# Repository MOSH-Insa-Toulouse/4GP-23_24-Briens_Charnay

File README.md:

# 4GP-23_24-Briens_Charnay

Projet réalisé sur l'année universitaire 2023/2024 de la formation 4GP, dans le cadre de l'Unité de Formation (UF) "du capteur au banc de test".
Le ci-présent fichier README donne tous les éléments de compréhension du projet global, ainsi que de toutes ses composantes. Cela est réalisé de sorte à permettre à l'utilisateur de reprendre tous les fichiers du présent dépôt GitHub, et de s'en servir.

## Sommaire

 - [Introduction](#introduction)
 - [Capteur à base de crayon graphite](#capteur-graphite)
 - [Circuit Electronique Analogique](#circuit-electronique-analogique)
 - [Kicad : réalisation du shield électronique PCB](#kicad)
 - [Banc de test](#banc-de-test)
 - [Interface Homme-Machine](#ihm)
 - [Programmation](#programmation)
 - [Datasheet](#datasheet)
***
## Introduction
### Contexte du projet

Nos travaux se sont basés sur les résultats d'une publication scientifique \[Cheng-Wei Lin et al., 2014]. Celle-ci étudiait l'utilisation de pistes de graphites sur des feuilles de papier comme capteurs de déformation, et donc de contrainte. Une telle technologie aurait de nombreux avantages :
 - Elle est sobre ;
 - Elle consomme peu d'énergie ;
 - Elle est simple d'utilisation ;
 - Elle est facilement réparable et remplaçable avec peu de ressources ;
 - Les ressources nécessaires sont disponibles au grand public pour un prix très réduit.

Du point de vue physique, la technologie se base sur les effets granulaires des couches de graphite déposées sur le papier : qui agissent comme des îlots conducteurs, séparés par une absence de graphite - non conductrice. Cela induit d'infimes capacités en très grand nombre. Lorsque le papier est déformé, la distance entre ces îlots varie, les capacités également. Cela se mesure sur la résistance du dispositif : dont l'évolution angulaire absolue varie linéairement.

### Contenu du projet

Comme annoncé par le nom de l'UF, notre projet a inclut toutes les étapes allant du capteur au bac de test, le tout en open source hardware. Les différentes phases clés du projet ont donc été, telles qu'annoncées en sommaire :
- le développement du capteur à jauge de contrainte à base de crayon graphite ;
- la conception d'un circuit analogique pour interfacer le capteur à jauge de contrainte;
- la programmation arduino de microcontrôleurs ;
- la réalisation d'une application android ;
- la réalisation d'un shield électronique PCB dédié à l'interface du capteur de contrainte ;
- la réalisation d'un banc de test.

Ces différentes étapes ne seront pas présentées dans un ordre temporel mais logique : de sorte à permettre pour chacune de comprendre l'intégralité des éléments.
***
## Capteur graphite
Le capteur graphite développé se présente sous la forme suivante, toutes les grandeurs sont données en mm :

On note le signal prévu pour chacun des pins :
- pin 1 : +5V
- pin 2 : sortie analogique
Les deux pins sont inversibles.

Les zones pointillées doivent être recouverte d'une épaisse couche de graphite, déposée par crayon.
Les pins utilisés sont supposés classiques, comme par exemple des pinces métalliques.
***
## Circuit Electronique Analogique

L'impédance de notre capteur graphite est de l'ordre du gigaOhm, les courants et les variations de courant à mesurer seront donc très faible. Afin que l'entrée convertisseur analogique numérique de l'arduino puisse détecter ces variations de tension, nous avons dû réaliser un circuit d'amplification. Nous avons choisi un montage transimpédance à deux étages en utilisant l'amplificateur opérationnel LTC 1050. Ce montage permet de convertir le courant en tension ainsi que de réaliser un gain conséquent. Le montage final, présenté ci-dessous, inclut aussi plusieurs filtres :

- R5 en entrée protège l'ampli opérationnel contre les décharges électrostatiques, en
forme avec C1 un filtre pour les bruits en tension
- C1 avec R1 forme un filtre pour le bruit en courant
- R2 sera interchangeable, pour permettre une adaptation du calibre
- C4 avec R3 forme un filtre actif
- C2 avec R6 forme le filtre de sortie
- C3 filtre le bruit d'alimentation

*Fichier associé* : Circuit_capteur_final.asc

***
## Kicad
La réalisation du shield électronique PCB nous avons utilisé le logiciel Kicad 8.0.

### Schematic

La première étape a été de réaliser le schematic du circuit electronique analogique en implantant les différents composants que nous avons vu dans la partie cirtuit electronique analogique. Nous avons uniquement remplacé le résistance R2 par le potentiomètre digital MCP-41050. Cela nous permet de faire varier la résistance R2 et donc d'avoir la possibilité de jouer sur le gain de l'amplificateur.

Nous avons ajouté plusieurs composants :

- Le capteur graphite
- Un capteur flex dans le but de le comparer avec notre solution lowtech
- Un écran OLED afin d'afficher les valeurs mesurées ainsi que la valeur de résistance du potentiomètre digital.
- Un module bluetooth HC-6 pour pouvoir communiquer avec une application Android
- Des boutons qui permettrons de se déplacer dans le menu et de selectionner un champ
- Le shield pour connecter l'arduino
- Un filtre passif pour les bruits venant de l'alimentation

*Fichier associé* : Shield_capteur.kicad_sch

***
### PCB

Nous avons ensuite pu implanter les différents composants sur le PCB comme présenté ci-dessous.

Les dimensionnements sont les suivants :
- La largeur des pistes est de 0,8mm
- Les pads circulaires pour les composants ont un diamètre de 2,54mm avec un trou circulaire de 0,8mm
- Les pads ovoïde pour les raccordements par pins ont une largeur de 2mm et une longueur de 2,54mm. Les pins de raccordements pour l'arduino nécessite un trou de 1mm de diamètre. Les pads pour les supports de plaques ont quand à eux un trou de 0,8mm

  Le plan de masse a été généré automatiquement par Kicad. En effectuant le test de vérification des règles de dessin, nous avons pu corriger des erreurs de placement ou de superposition des composants.
L'organisation de notre PCB nous a permis de ne pas avoir besoin de créer des VIAs. Nous avons ensuite pu imprimer le masque de notre circuit afin de réaliser le shield par voie chimique.

*Fichier associé* : Shield_capteur.kicad_pcb

***
## Banc de test

Afin de réaliser des mesures précises et reproductibles, nous avons réalisé un banc de test complet. Celui-ci est composé de différents composants présentés ci-dessous :

Comme présenté sur la photo détaillée, nous avons utilisé un second arduino pour réaliser notre banc de test. Ce dernier contrôle le servomoteur qui permet l'enroulement d'un cable autour d'une poulie. Cela permet de plier d'un pas choisi, de manière très contrôlé et reproductible le capteur graphite. Ce second arduino est branché sur les pins l'arduino principal afin qu'une synchronisation entre les changements de degrés et la mesure puisse s'effectuer. Vous trouverez plus de détails sur la communication entre les deux arduino dans la partie programmation. 

***
## IHM
L'Interface Homme-Machine (ou IHM) correspond à tous les éléments permettant la communication entre l'utilisateur et les composants software.
### Boutons et écran OLED
Trois boutons ainsi qu'un écran OLED sont directement présents sur le shield :

Du haut vers le bas, les trois boutons correspondent aux actions :
- select ;
- up ;
- down.

L'écran OLED affiche un total de 4 champs. Les deux premiers sont modifiables, les deux derniers correspondent à des mesures réalisées.
- la valeur du potentiomètre digital ;
- l'unité de mesure ;
- la valeur mesurée dans cette unité par le capteur graphite ;
- la valeur mesurée dans cette unité par le Flex Sensor, capteur commercial.

L'utilisateur contrôle un curseur, celui-ci a deux états disponibles : "- xyz -" et "< xyz >". Le premier correspond au choix du champ à modifier : il permet à l'utilisateur de choisir s'il souhait modifier la valeur du potentiomètre ou l'unité de mesure. Le deuxième correspond à la modification du champ actuel : les boutons up et down permettent alors de se déplacer parmis les différentes options proposées pour le champ actuel. La pression du bouton select permet de passer d'un état à l'autre.
### Application Android
Il est également possible de communiquer avec l'arduino via une application android connectée en bluetooth. Celle-ci se présente ainsi :

Chaque ligne possède un rôle :
- la première, "Bluetooth et fichier" : permet de se connecter à l'arduino en bluetooth, de s'en déconnecter, et d'exporter les données du graphe. L'export se fait dans un fichier texte généré dans le téléphone ;
- la deuxième, "Contrôle d'acquisition" : permet de lancer l'acquisition de données, de la stopper, ou de lancer un test automatisé de la jauge (voir banc de test) ;
- la troisième est le graphe sur lequel apparaissent les données récoltées ;
- la quatrième, "Contrôle graphique" : permet de remettre le graphique à zéro, et de changer l'unité de mesure en volts, en ohms, ou en degrés ;
- la cinquième, "Nombre de points" : permet de choisir le nombre de point maximum à enregistrer et afficher sur le graphique.

*Fichiers associés* :
- application android/AppMOSH1.apk
- application android/CodeAppAndroid.aia
***
## Programmation
### Protocoles de communication
Au sein de notre projet, nous avons mis en place deux protocoles de communication : entre le téléphone et l'arduino du capteur graphite (bluetooth), ainsi qu'entre cette dernière et l'arduino du banc de test (électronique directe).
#### Communication Bluetooth
Dans le cadre de la communication bluetooth entre le téléphone et l'arduino du capteur graphite, les données sont transmises sous format ASCII, par des messages de 16 caractères, sous le format suivent :

Le téléphone est maître de la communication, l'arduino joue le rôle d'esclave. Le caractère "commande" permet de transmettre une information ou ordre spécifique, nous notons les différentes possibilités :

Du téléphone vers l'arduino :
- d : demander l'envoie d'un message ;
- V : choix d'une mesure en volts ;
- O : choix d'une mesure en ohms ;
- D : choix d'une mesure en degrés ;
- t : lancement d'un test automatisé.

De l'arduino vers le téléphone :
- V : message contenant une donnée en volts ;
- O : message contenant une donnée en ohms ;
- D : message contenant une donnée en degrés ;
- c : information du lancement d'un test automatisé ;
- f : information de la fin d'un test automatisé.
#### Communication électronique directe
Dans le cadre de la communication électronique directe entre les arduinos du capteur graphite et du banc de test, deux lignes de communication sont utilisées : chacune contrôlée par une carte arduino. Ce protocole de communication permet de synchroniser le lancement des tests automatisés entre le banc de test, et l'enregistrement des mesures sur le téléphone. Le chronogramme se présente ainsi :

Nous détaillons chaque évolution :
- état initial : les deux lignes sont à l'état down ;
- l'arduino du capteur reçoit l'ordre de l'application de lancer le test automatisé, sa ligne passe à up ;
- l'arduino du banc de test lit l'information, lance le test, et passe sa ligne à up ;
- l'arduino du capteur lit que le test a bien été lancé, passe sa ligne à down, et envoie l'information à l'application ;
- une fois le test terminé, l'arduino du banc de test passe sa ligne à down ;
- l'arduino du capteur lit que le test est terminé, et envoie l'information à l'application.
### Programme Arduino
Deux programmes arduinos ont été créés, pour les deux cartes utilisées dans ce projet : celle du shield PCB (connectée au capteur graphite), et celle du banc de test. Nous détaillons leur fonctionnement.
#### Arduino du capteur graphite
Le fonctionnement général de l'arduino du capteur graphite suit la logique présentée dans le schéma suivant :

Le choix a été fait de réaliser un debouncing des boutons entièrement software.

*Fichier associé* : programme_complet/programme_complet.ino
#### Arduino du banc de test
L'arduino du banc de test possède un programme bien plus simple et direct. Celui-ci suit la structure suivante :
- ajuster la position du Servomoteur : à 0 si aucun test n'est en cours, sinon une autre valeur variable ;
- lire et écrire sur les lignes de communication avec l'arduino du capteur graphite.

*Fichier associé* : programme_second_arduino/prog_second_arduino/prog_second_arduino.ino
***
## Datasheet
Finalement, la combinaison de tous ces éléments a permis la récolte de données, et la rédaction d'une datasheet complète du capteur graphite. Celle-ci est divisée en plusieurs catégories :
- Caractéristiques générales : points clés à l'avantage du capteur ;
- Description : description de la physique du fonctionnement du capteur, développement de ses avantages clés, objectif du développement du capteur ;
- Description des pins : description des pins et signaux du capteur, permettant son implémentation électronique ;
- Dimensions : description matérielle du capteur ;
- Spécifications : description technique concise du capteur ;
- Conditions d'utilisation standard : conditions environnementales classiques, pour lesquelles le capteur a été développé ;
- Caractéristiques électriques : pour les différentes variantes du capteur (en fonction du crayon utilisé), évolution de la résistance absolue et relative en fonction de l'angle ;
- Utilisation typique : exemple d'un circuit électronique typique dans lequel implémenter le capteur pour en tirer des données.
Ce circuit électronique typique correspond à celui que nous avons réalisé sur l'arduino du capteur, et présenté précédemment.

Cette datasheet permet à tout nouvel arrivant de produire et d'utiliser notre capteur graphite : dans un esprit Low-Tech et Open Source.

*Fichier associé* : Datasheet_strain_gauge-MCharnay-ABriens.pdf

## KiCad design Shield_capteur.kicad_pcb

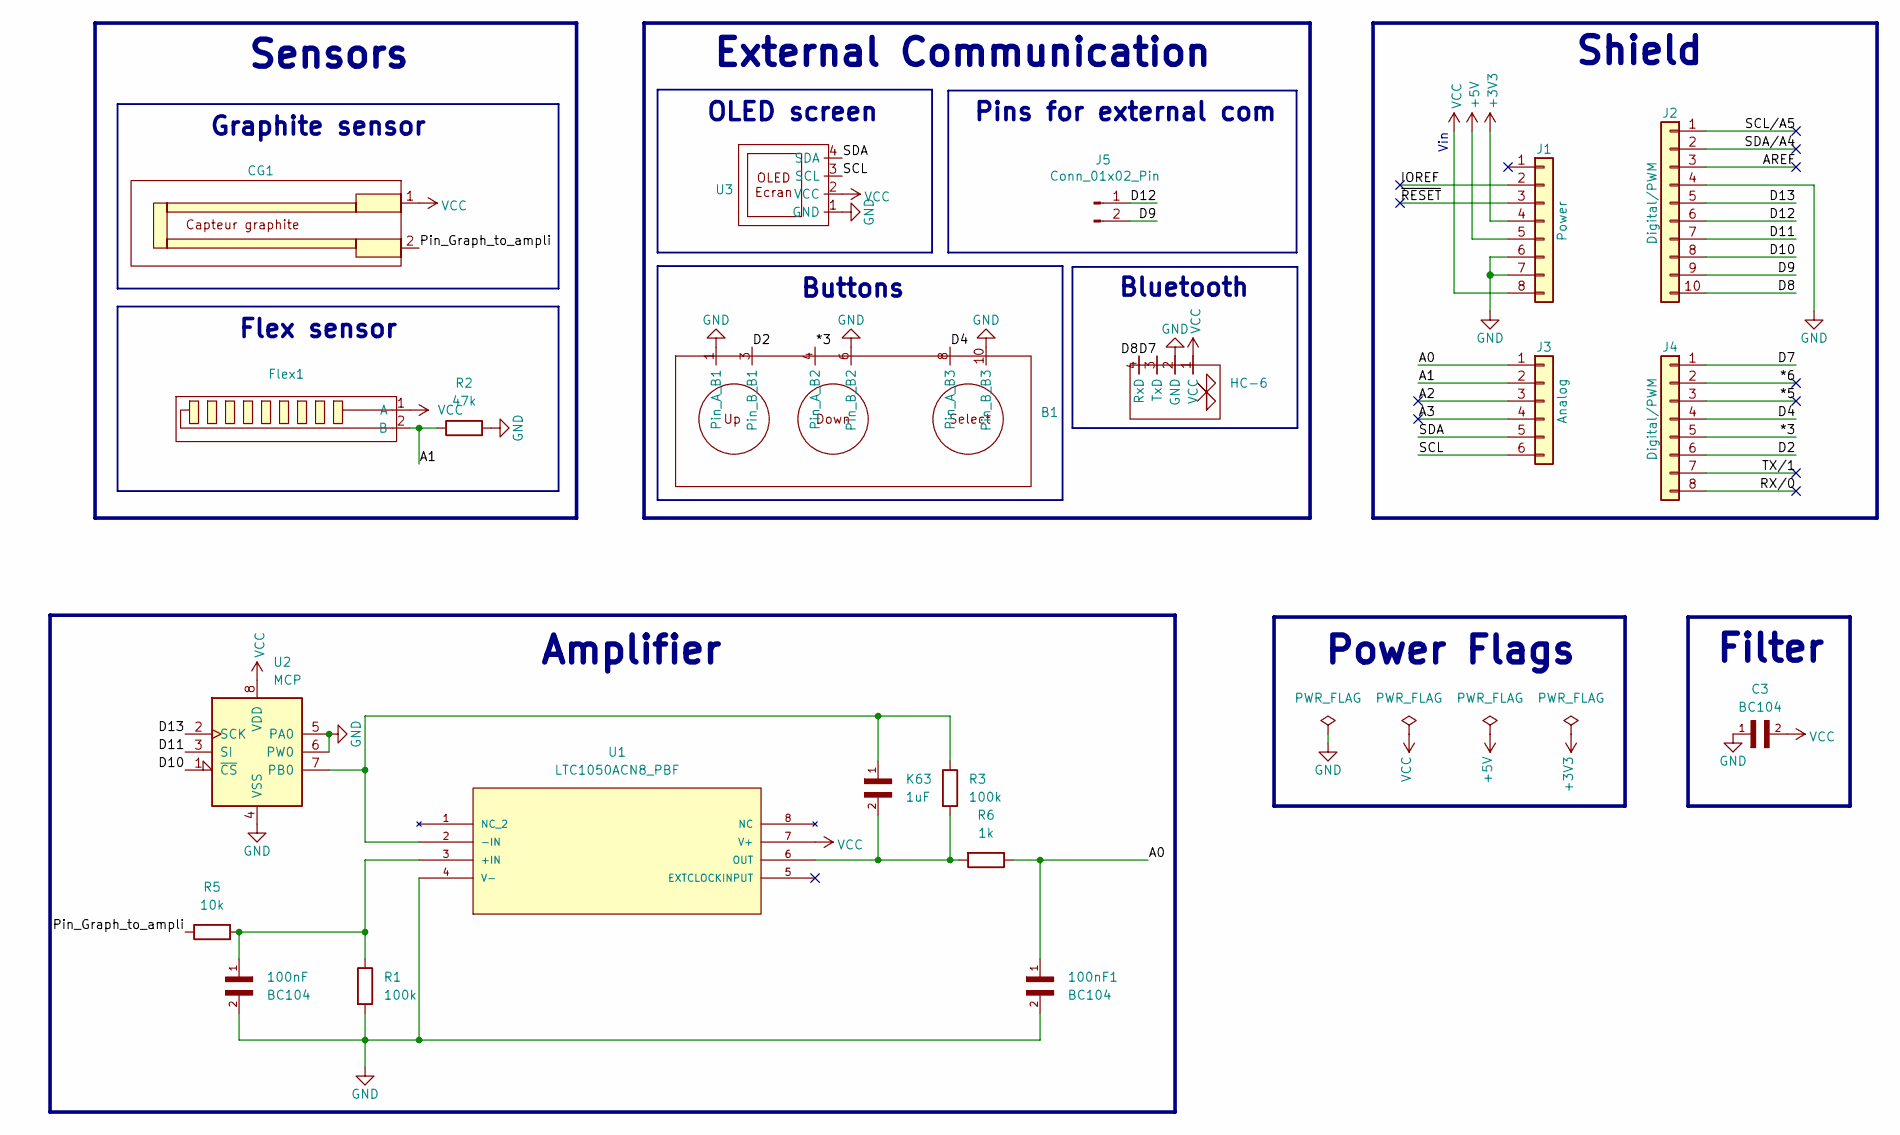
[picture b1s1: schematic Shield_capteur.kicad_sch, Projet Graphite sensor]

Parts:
100nF1: BC104; C_Disc_D5.0mm_W2.5mm_P5.00mm
B1: Boutons_x3
BC104: 100nF; C_Disc_D5.0mm_W2.5mm_P5.00mm
C3: BC104; C_Disc_D5.0mm_W2.5mm_P5.00mm
CG1: PinSocket_1x02_P2.54mm_Vertical
Flex1: PinSocket_1x02_P2.54mm_Vertical
HC-6: PinSocket_1x04_P2.54mm_Vertical
J1: Power; PinSocket_1x08_P2.54mm_Vertical
J2: Digital/PWM; PinSocket_1x10_P2.54mm_Vertical
J3: Analog; PinSocket_1x06_P2.54mm_Vertical
J4: Digital/PWM; PinSocket_1x08_P2.54mm_Vertical
J5: Conn_01x02_Pin; PinSocket_1x02_P2.54mm_Vertical
K63: 1uF; C_Rect_L7.0mm_W4.5mm_P5.00mm
R1, R3: 100k; R_Axial_DIN0207_L6.3mm_D2.5mm_P10.16mm_Horizontal
R2: 47k; R_Axial_DIN0207_L6.3mm_D2.5mm_P10.16mm_Horizontal
R5: 10k; R_Axial_DIN0207_L6.3mm_D2.5mm_P10.16mm_Horizontal
R6: 1k; R_Axial_DIN0207_L6.3mm_D2.5mm_P10.16mm_Horizontal
U1: LTC1050ACN8_PBF; PDIP-8_N; MANUFACTURER_PART_NUMBER ltc1050acn8
U2: MCP; PDIP-8_N
U3: PinSocket_1x04_P2.54mm_Vertical

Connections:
+3V3: J1.4
+5V: J1.5
/*3: B1.4 (Pin_A_B2), J4.5
/*5: J4.3
/*6: J4.2
/A0: 100nF1.1, J3.1, R6.1
/A1: Flex1.2 (B), J3.2, R2.1
/A2: J3.3
/A3: J3.4
/AREF: J2.3
/D2: B1.3 (Pin_B_B1), J4.6
/D4: B1.8 (Pin_A_B3), J4.4
/D7: HC-6.3 (TxD), J4.1; also elsewhere on the board
/D8: HC-6.4 (RxD), J2.10; also elsewhere on the board
/D9: J2.9, J5.2
/D10: J2.8, U2.1 (~CS)
/D11: J2.7, U2.3 (SI)
/D12: J2.6, J5.1
/D13: J2.5, U2.2 (SCK)
/IOREF: J1.2
/RX/0: J4.8
/SCL: J3.6, U3.3 (SCL)
/SCL/A5: J2.1
/SDA: J3.5, U3.4 (SDA)
/SDA/A4: J2.2
/TX/1: J4.7
/~RESET: J1.3
GND: 100nF1.2, B1.1 (Pin_A_B1), B1.6 (Pin_B_B2), B1.10 (Pin_B_B3), BC104.2, C3.1, HC-6.2 (GND), J1.6, J1.7, J2.4, R1.2, R2.2, U1.4 (V-), U2.4 (VSS), U2.5 (PA0), U2.6 (PW0), U3.1 (GND); also elsewhere on the board
unnamed: CG1.2, R5.1
unnamed: BC104.1, R1.1, R5.2, U1.3 (+IN)
unnamed: K63.1, R3.1, U1.2 (-IN), U2.7 (PB0)
unnamed: K63.2, R3.2, R6.2, U1.6 (OUT)
VCC: C3.2, CG1.1, Flex1.1 (A), HC-6.1 (VCC), J1.8, U1.7 (V+), U2.8 (VDD), U3.2 (VCC); also elsewhere on the board

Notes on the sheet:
Graphite sensor
Vin
Amplifier
Flex sensor
Filter
Power Flags
Pins for external com
Bluetooth
Shield
Sensors
OLED screen
External Communication
Buttons

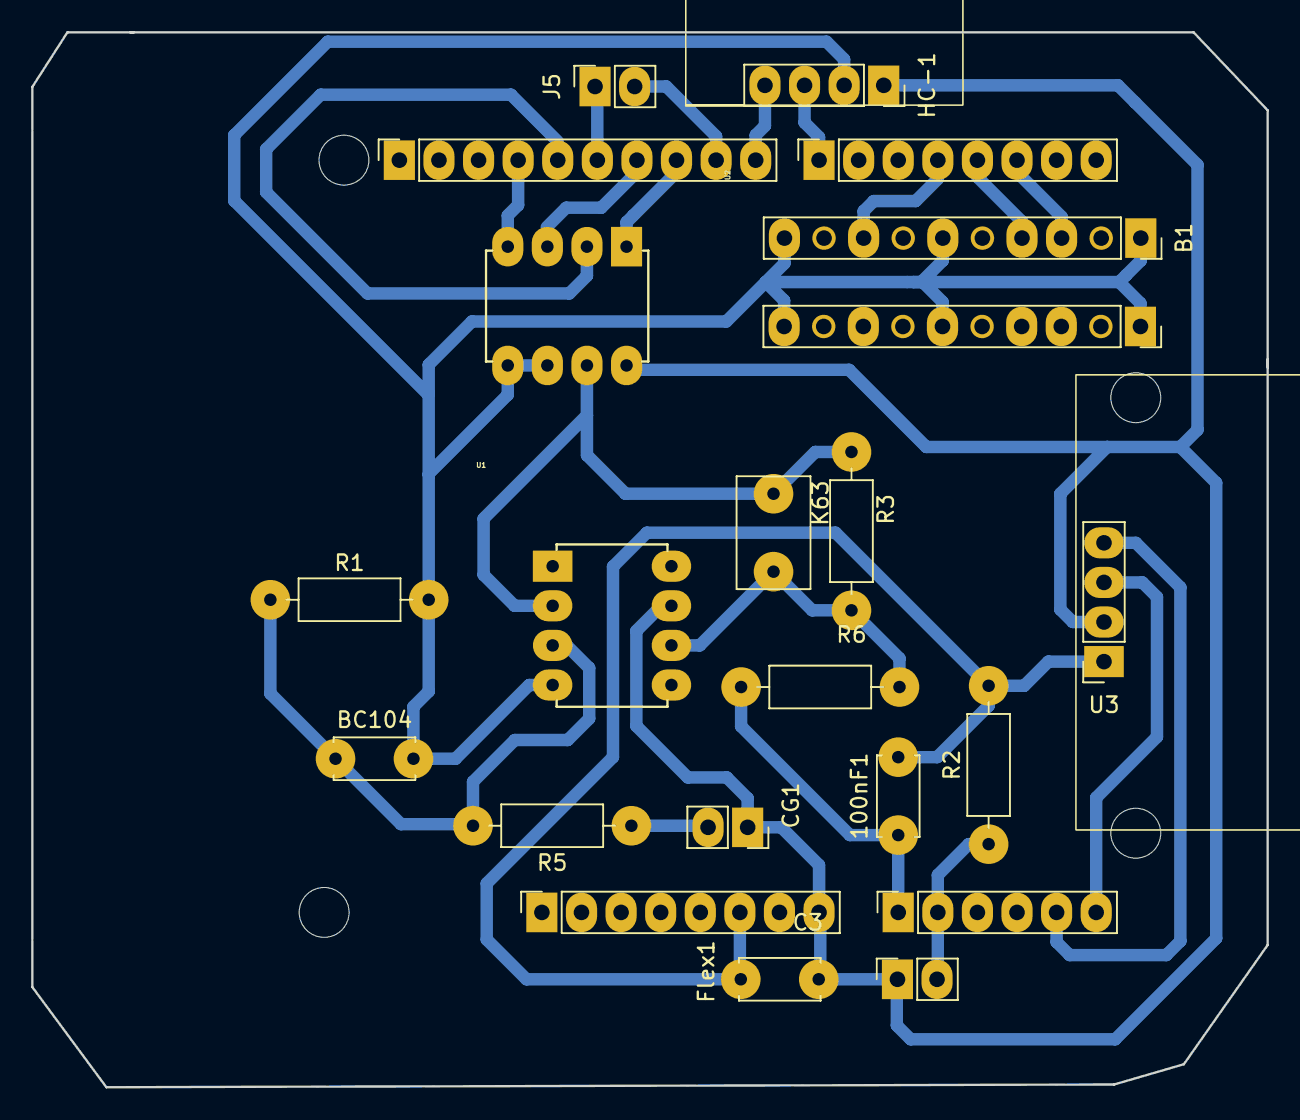
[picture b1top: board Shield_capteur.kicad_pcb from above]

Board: 2 copper layers, 79.2 x 67.7 mm, 25 parts (0 on the bottom side), 20 nets.

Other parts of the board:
HC-1: PinSocket_1x04_P2.54mm_Vertical
MH1, MH2, MH3, MH4: MountingHole_3.2mm

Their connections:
/D7: HC-1.3 (TxD); also elsewhere on the board
/D8: HC-1.4 (RxD); also elsewhere on the board
GND: HC-1.2 (GND); also elsewhere on the board
VCC: HC-1.1 (VCC); also elsewhere on the board

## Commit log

2024-03-06 test initial
2024-03-06 Suppression test
2024-03-06 Fichier base shield kicad
2024-03-06 Verification fonctionnement
2024-03-06 fin verification
2024-03-06 correction commentaires
2024-03-06 Réalisation capteur graphite
2024-03-06 test fonctionnement bis
2024-03-06 Changement mineur
2024-03-06 Avancée sur le shield, schéma +footprint
2024-03-11 maj dossier Shield Capteur
2024-03-11 Progrès TD Datasheet
2024-03-13 Fin de la schematic
2024-03-13 Changement pastilles PCB
2024-03-14 Avancé PCB positionnement de tous les composants
2024-03-16 Fin du placement des composants et pistes sur PCB. Quelques erreurs mineures à régler
2024-03-18 Correction du PCB il reste connection RFlex
2024-03-20 Changement de la largeur des pistes de 0.6mm à 0.8mm
2024-03-20 Ajout programme Arduino
2024-03-21 optimisation memoire et ajout servo (commentaire)
2024-03-22 Ajout lien second Arduino
2024-03-26 Implantation communication Bluetooth avec application
2024-03-27 Implantation Arduino avec PCB
2024-03-31 implantation conversion mesure
2024-03-31 implantation communication unite avec app + selection unite depuis app
2024-03-31 ajout application android sur le git
2024-04-05 ajout flex sensor sur OLED + implantation controle nb points sur app
2024-04-18 fin kicad ajout liaison second arduino
2024-04-19 Début du programme pour le second arduino programmation du servomoteur
2024-04-19 Ajout fonctions de synchronisation Arduino
2024-04-19 correction bug synchronisation programme principal
2024-04-19 ajout INPUT PULLUP
2024-04-19 finalisation synchronisation arduino, mise à jour app & ajout fichier projet app
2024-04-21 Mise en forme shematic et rajout valeurs MCP
2024-04-21 app ajout export data
2024-05-16 Redaction structure & introduction README.md
2024-05-18 Complétion partielle README.md
2024-05-20 Ajout pdf datasheet
2024-05-20 Ajout section datasheet README
2024-05-25 Ajout_fichiers
2024-05-25 correction datasheet, ajout arduino calcul angle

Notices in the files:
parts and their libraries:
COPYRIGHT: Copyright C 2016 Accelerated Designs. All rights reserved
